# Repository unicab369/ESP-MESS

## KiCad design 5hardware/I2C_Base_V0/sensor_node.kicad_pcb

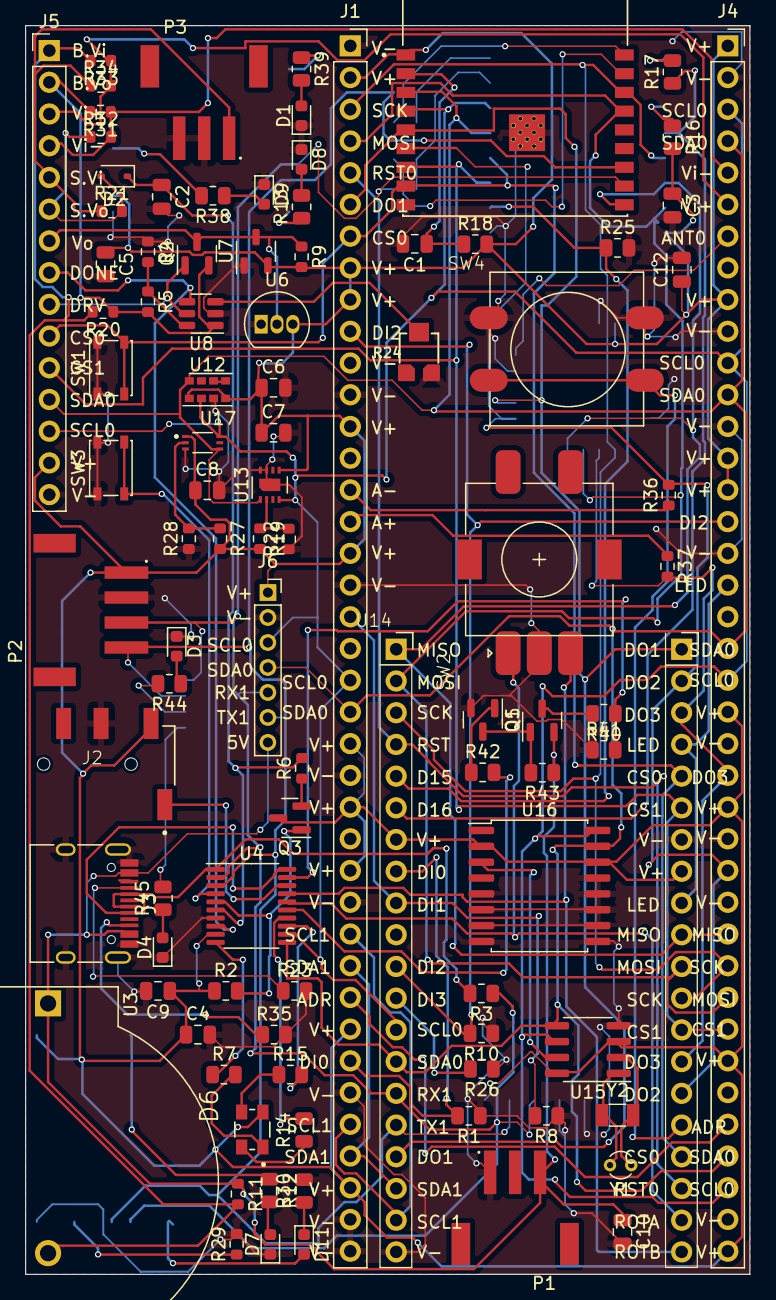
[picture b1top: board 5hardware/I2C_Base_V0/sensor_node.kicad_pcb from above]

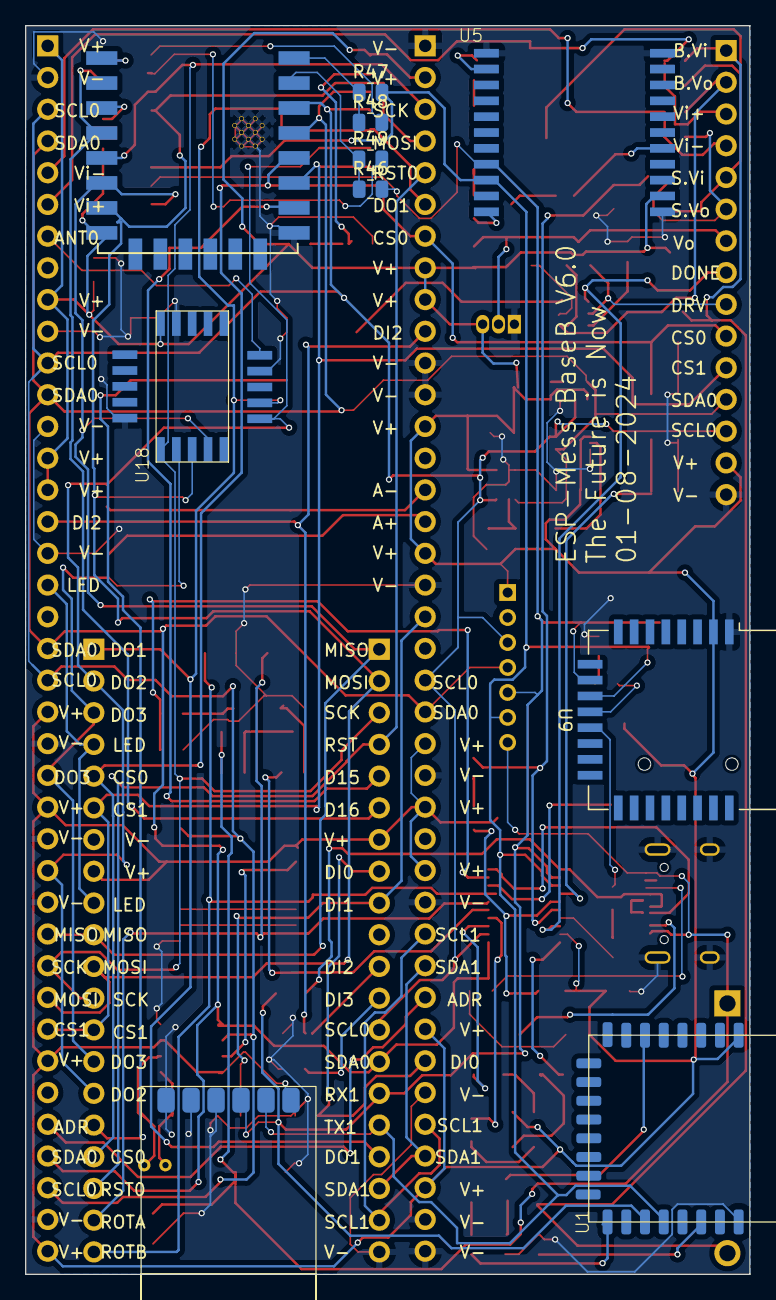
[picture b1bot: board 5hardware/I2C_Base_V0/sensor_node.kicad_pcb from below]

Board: 2 copper layers, 58.0 x 100.0 mm, 106 parts (10 on the bottom side), 91 nets.

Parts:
C1, C2, C3, C4, C5, C6, C7, C8, C9, C10, C12: C; C_0805_2012Metric
D1, D3, D4, D7, D8, D9, D11: LED; LED_0603_1608Metric
D2: D_Schottky; D_SOD-323
D6: LL-R3528RGBC-008-B; LED_LL-R3528RGBC-008-B
J1, J4: Conn_01x39_Socket; PinSocket_1x39_P2.54mm_Vertical
J2: PJ-320D-A; PJ-320D
J3: USB_C_Receptacle_USB2.0; USB_C_Receptacle_HRO_TYPE-C-31-M-12
J5: Conn_01x15_Pin; PinHeader_1x15_P2.54mm_Vertical
J6: Conn_01x07_Pin; PinSocket_1x07_P2.00mm_Vertical
P1, P3: S3B-PH-SM4-TB; JST_S3B-PH-SM4-TB
P2: S4B-PH-SM4-TB; JST_S4B-PH-SM4-TB
Q1, Q2, Q3: Si2371EDS; SOT-23
Q5: MMBT5551L; SOT-23
R1, R2, R3, R7, R8, R10, R12, R13, R14, R15, R16, R17, R18, R23, R25, R26, R30, R35, R38, R39, R40, R41, R42, R43, R44, R45, R46, R47, R48, R49: R; R_0805_2012Metric
R4, R5, R6, R9, R11, R19, R20, R21, R22, R27, R28, R29, R31, R32, R33, R34, R36, R37: R; R_0603_1608Metric
R24: EVM3ESX50B12; EMV3ESX50B12
SW1, SW3: SW_Push; SW_SPST_PTS810
SW2: RotaryEncoder; RotaryEncoder_E11
SW4: SW_Push; ButtonSwitch12mm_SMD
U1: JDY-Base
U2: ESP32-C3-WROOM-02; MODULE_ESP32-C3-WROOM-02-H4
U3: CR2450; BatteryHolder_ComfortableElectronic_CH273-2450_1x2450
U4: CH32V003F4P6; TSSOP-20_4.4x6.5mm_P0.65mm
U5: E104-BT07
U6: MCP1700x-330xxTO; TO-92_Inline
U7: XC6206PxxxMR; SOT-23-3
U8: TPL5110; SOT-23-6
U9: E18-MS1-PCB
U10: ESP-12F; ESP12_SMD
U11: JDY-41
U12: APDS-9960; Avago_APDS-9960
U13: SHT31-DIS; Sensirion_DFN-8-1EP_2.5x2.5mm_P0.5mm_EP1.1x1.7mm
U14: Lolin_Base; LolinBase
U15: DS1307Z+; SOIC-8_3.9x4.9mm_P1.27mm
U16: DS3231M; SOIC-16W_7.5x10.3mm_P1.27mm
U17: BH1750FVI-TR; XDCR_BH1750FVI-TR
U18: E220-900MM
Y1: Crystal; Crystal_Round_D1.5mm_Vertical
Y2: Crystal; Crystal_SMD_3215-2Pin_3.2x1.5mm

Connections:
+5V: C10.1, J3.A4 (VBUS), J3.A9 (VBUS), J3.B4 (VBUS), J3.B9 (VBUS), J6.7, P1.3, Q1.2 (S), R11.1, R43.1, U3.1 (+)
A+: J1.16, R37.1
A-: J1.15, R36.1
ADDR: J1.31, J4.35
ANT0: J4.7, U18.6 (ANT)
Bat-Vi: J5.1, R11.2, R20.2, R33.2, U3.2 (-)
Bat-Vo: J5.2, Q2.2 (S), R5.2, R20.1, R31.2, U8.1 (VDD)
CS0: J1.7, J5.10, SW1.2, U2.8 (GPIO9), U10.12 (GPIO0), U14.25 (X), U14.37 (IO_0)
CS1: J4.32, J5.11, U2.7 (GPIO8), U10.11 (GPIO2), U14.26 (X), U14.33 (IO_5)
D15: R25.1, U10.10 (GPIO15), U14.5 (X)
D16: R17.1, U10.4 (GPIO16), U14.6 (X)
D+: J3.A6 (D+), J3.B6 (D+), U4.20 (PD3)
D-: J3.A7 (D-), J3.B7 (D-), R3.2, U4.1 (PD4)
DI0: J1.33, R1.2, U14.8 (IO_36)
DI1: J1.19, R8.2, U14.9 (IO_39)
DI2: J1.10, J4.16, R10.2, U14.11 (IO_34)
DI3: R26.2, U14.12 (IO_35)
DO1: J1.6, U2.5 (GPIO6), U14.17 (IO_27), U14.21 (X), U18.9 (TXE)
DO2: J4.27, R36.2, U2.6 (GPIO7), U14.22 (X), U14.35 (IO_16), U18.10 (RXE)
DO3: J4.24, R37.2, U14.23 (X), U14.34 (IO_17), U18.14 (CS)
DONE: J5.8, U4.8 (PD0), U8.4 (DONE)
DRV: J5.9, Q2.1 (G), U8.5 (DRV)
EN: R16.1, U10.3 (CH_PD)
GND: C1.2, C2.2, C3.2, C4.2, C5.2, C6.2, C7.2, C8.2, C9.2, C10.2, C12.2, D1.1 (K), D3.1 (K), D4.1 (K), D7.1 (K), D8.1 (K), D9.1 (K), J1.1, J1.11, J1.12, J1.18, J1.24, J1.28, J1.34, J1.38, J1.39, J2.3, J3.A1 (GND), J3.A12 (GND), J3.B1 (GND), J3.B12 (GND), J3.S1 (SHIELD), J4.2, J4.10, J4.13, J4.17, J4.23, J4.26, J4.28, J4.38, J5.15, J6.2, P1.1, P2.2, P3.2, P3.3, Q5.2 (E), R1.1, R4.1, R8.1, R10.1, R22.1, R23.2, R24.3, R25.2, R26.1, R28.1, R29.2, R30.2, R35.2, R41.1, SW1.1, SW2.C, SW3.1, SW4.1, U1.24 (GND), U2.9 (GND), U2.19 (GND), U4.7 (VSS), U5.1 (GND), U5.12 (GND), U5.22 (GND), U6.1 (GND), U7.1 (GND), U8.2 (GND), U9.1 (GND), U10.9 (GND), U11.4 (SET), U11.5 (CS), U11.6 (GND), U12.6 (GND), U13.7 (R), U13.8 (VSS), U13.9 (VSS), U14.20 (GND), U14.27 (X), U15.4 (GND), U16.5 (GND), U16.6 (GND), U16.7 (GND), U16.8 (GND), U16.9 (GND), U16.10 (GND), U16.11 (GND), U16.12 (GND), U16.13 (GND), U17.3 (GND), U18.2 (GND), U18.7 (GND), U18.16 (GND)
LED: J4.18, U14.24 (X), U14.29 (IO_22)
MISO: J4.29, U2.10 (GPIO10), U10.6 (GPIO12), U14.1 (X), U14.30 (IO_19), U18.12 (MISO)
MOSI: J1.4, J4.31, U2.15 (GPIO3/ADC1_CH3), U10.7 (GPIO13), U14.2 (X), U14.31 (IO_23), U18.13 (MOSI)
unnamed: D1.2 (A), R39.2
unnamed: C2.1, D2.1 (K), R6.2, U4.6 (PA2)
unnamed: D3.2 (A), R44.1
unnamed: D4.2 (A), R45.1
unnamed: D6.1, R7.2
unnamed: D6.3, R15.1
unnamed: D6.4, R14.1
unnamed: D7.2 (A), R12.2
unnamed: D8.2 (A), R13.2
unnamed: D9.2 (A), R38.1
unnamed: D11.2 (A), U1.17 (ALED)
unnamed: D11.1 (K), R30.1
unnamed: J3.A5 (CC1), R23.1
unnamed: J3.B5 (CC2), R35.1
unnamed: Q1.3 (D), R40.2
unnamed: Q1.1 (G), Q5.3 (C), R43.2
unnamed: Q3.1 (G), R2.2, U4.5 (PA1)
unnamed: Q3.2 (S), R6.1
unnamed: Q5.1 (B), R42.1
unnamed: R29.1, U1.22 (PWRC)
unnamed: R12.1, U1.6 (STAT)
unnamed: C1.1, R18.1, U2.2 (EN/CHIP_PU)
unnamed: R7.1, U4.10 (PC0)
unnamed: R15.2, U4.13 (PC3)
unnamed: R14.2, U4.14 (PC4)
unnamed: R42.2, U4.15 (PC5)
unnamed: SW3.2, U4.4 (PD7)
unnamed: R38.2, U5.16 (P7)
unnamed: R39.1, U5.2 (P19)
unnamed: R13.1, U5.11 (P32)
unnamed: R24.2, U8.3 (DELAY/M_DRV)
unnamed: R4.2, R5.1, U8.6 (EN/ONE_SHOT)
unnamed: R45.2, U9.13 (P1.2)
unnamed: R44.2, U9.12 (P1.3)
unnamed: R46.1, R49.1, U10.15 (RXD)
unnamed: R47.1, R48.1, U10.16 (TXD)
unnamed: U12.3 (LDR), U12.4 (LED_K)
unnamed: R19.1, R22.2, U13.2 (ADDR)
unnamed: SW4.2, U14.36 (IO_4)
unnamed: U15.7 (SQW/OUT), U16.3 (~INT/SQW)
unnamed: U15.1 (X1), Y1.2, Y2.2
unnamed: U15.2 (X2), Y1.1, Y2.1
unnamed: R27.1, R28.2, U17.2 (ADDR)
PD2: R40.1, R41.2, U4.19 (PD2)
ROTA: SW2.A, U4.16 (PC6), U14.39 (IO_15)
ROTB: SW2.B, U4.17 (PC7), U14.40 (IO_13)
RST0: J1.5, U14.4 (X), U14.38 (IO_2)
RST1: R17.2, U10.1 (REST)
RX1: J6.5, P2.3, R3.1, R46.2, U1.19 (TX), U2.11 (GPIO20/U0RXD), U4.2 (PD5), U5.8 (TX), U9.10 (P1.5), U11.3 (TX), U14.15 (IO_25)
RX2: R48.2, U2.18 (GPIO0/ADC1_CH0/XTAL_32K_P)
SCK: J1.3, J4.30, U2.16 (GPIO2/ADC1_CH2), U10.5 (GPIO14), U14.3 (X), U14.32 (IO_18), U18.15 (SCK)
SCL0: J1.21, J4.3, J4.11, J4.21, J4.37, J5.13, J6.3, U2.4 (GPIO5/ADC2_CH0), U4.12 (PC2), U10.14 (GPIO5), U12.7 (SCL), U13.4 (SCL), U14.13 (IO_32), U15.6 (SCL), U16.16 (SCL), U17.6 (SCL)
SCL1: J1.29, J1.35, U14.19 (IO_12)
SDA0: J1.22, J4.4, J4.12, J4.20, J4.36, J5.12, J6.4, U2.3 (GPIO4/ADC1_CH4), U4.11 (PC1), U10.13 (GPIO4), U12.1 (SDA), U13.1 (SDA), U14.14 (IO_33), U15.5 (SDA), U16.15 (SDA), U17.4 (SDA)
SDA1: J1.30, J1.36, U14.18 (IO_14)
SWIO: J2.1, U4.18 (PD1)
Solar_Vi: J5.5, P3.1, R21.1, R34.1
Solar_Vo: D2.2 (A), J5.6, R21.2, R32.1
TX1: J6.6, P2.4, R47.2, U1.20 (RX), U2.12 (GPIO21/U0TXD), U4.3 (PD6), U5.9 (RX), U9.11 (P1.4), U11.2 (RX), U14.16 (IO_26)
TX2: R49.2, U2.17 (GPIO1/ADC1_CH1/XTAL_32K_N)
VCC: C3.1, C4.1, C5.1, C6.1, C7.1, C8.1, C9.1, C12.1, D6.2, J1.2, J1.8, J1.9, J1.13, J1.17, J1.23, J1.25, J1.27, J1.32, J1.37, J2.2, J4.1, J4.9, J4.14, J4.15, J4.22, J4.25, J4.33, J4.39, J5.14, J6.1, P2.1, Q3.3 (D), R2.1, R9.2, R16.2, R18.2, R19.2, R27.2, U1.1 (VCC), U2.1 (3V3), U4.9 (VDD), U5.13 (VDD), U6.3 (VO), U7.2 (VO), U9.2 (VDD), U10.8 (VCC), U11.1 (VCC), U12.5 (LED_A), U12.8 (VCC), U13.5 (VDD), U14.7 (X), U14.28 (VCC), U15.3 (VBAT), U15.8 (VCC), U16.2 (VCC), U16.14 (VBAT), U17.1 (VCC), U18.1 (VCC)
Vi+: J4.6, J5.3, R33.1, R34.2
Vi-: J4.5, J5.4, R31.1, R32.2
Vo: J5.7, Q2.3 (D), R9.1, U6.2 (VI), U7.3 (VI)

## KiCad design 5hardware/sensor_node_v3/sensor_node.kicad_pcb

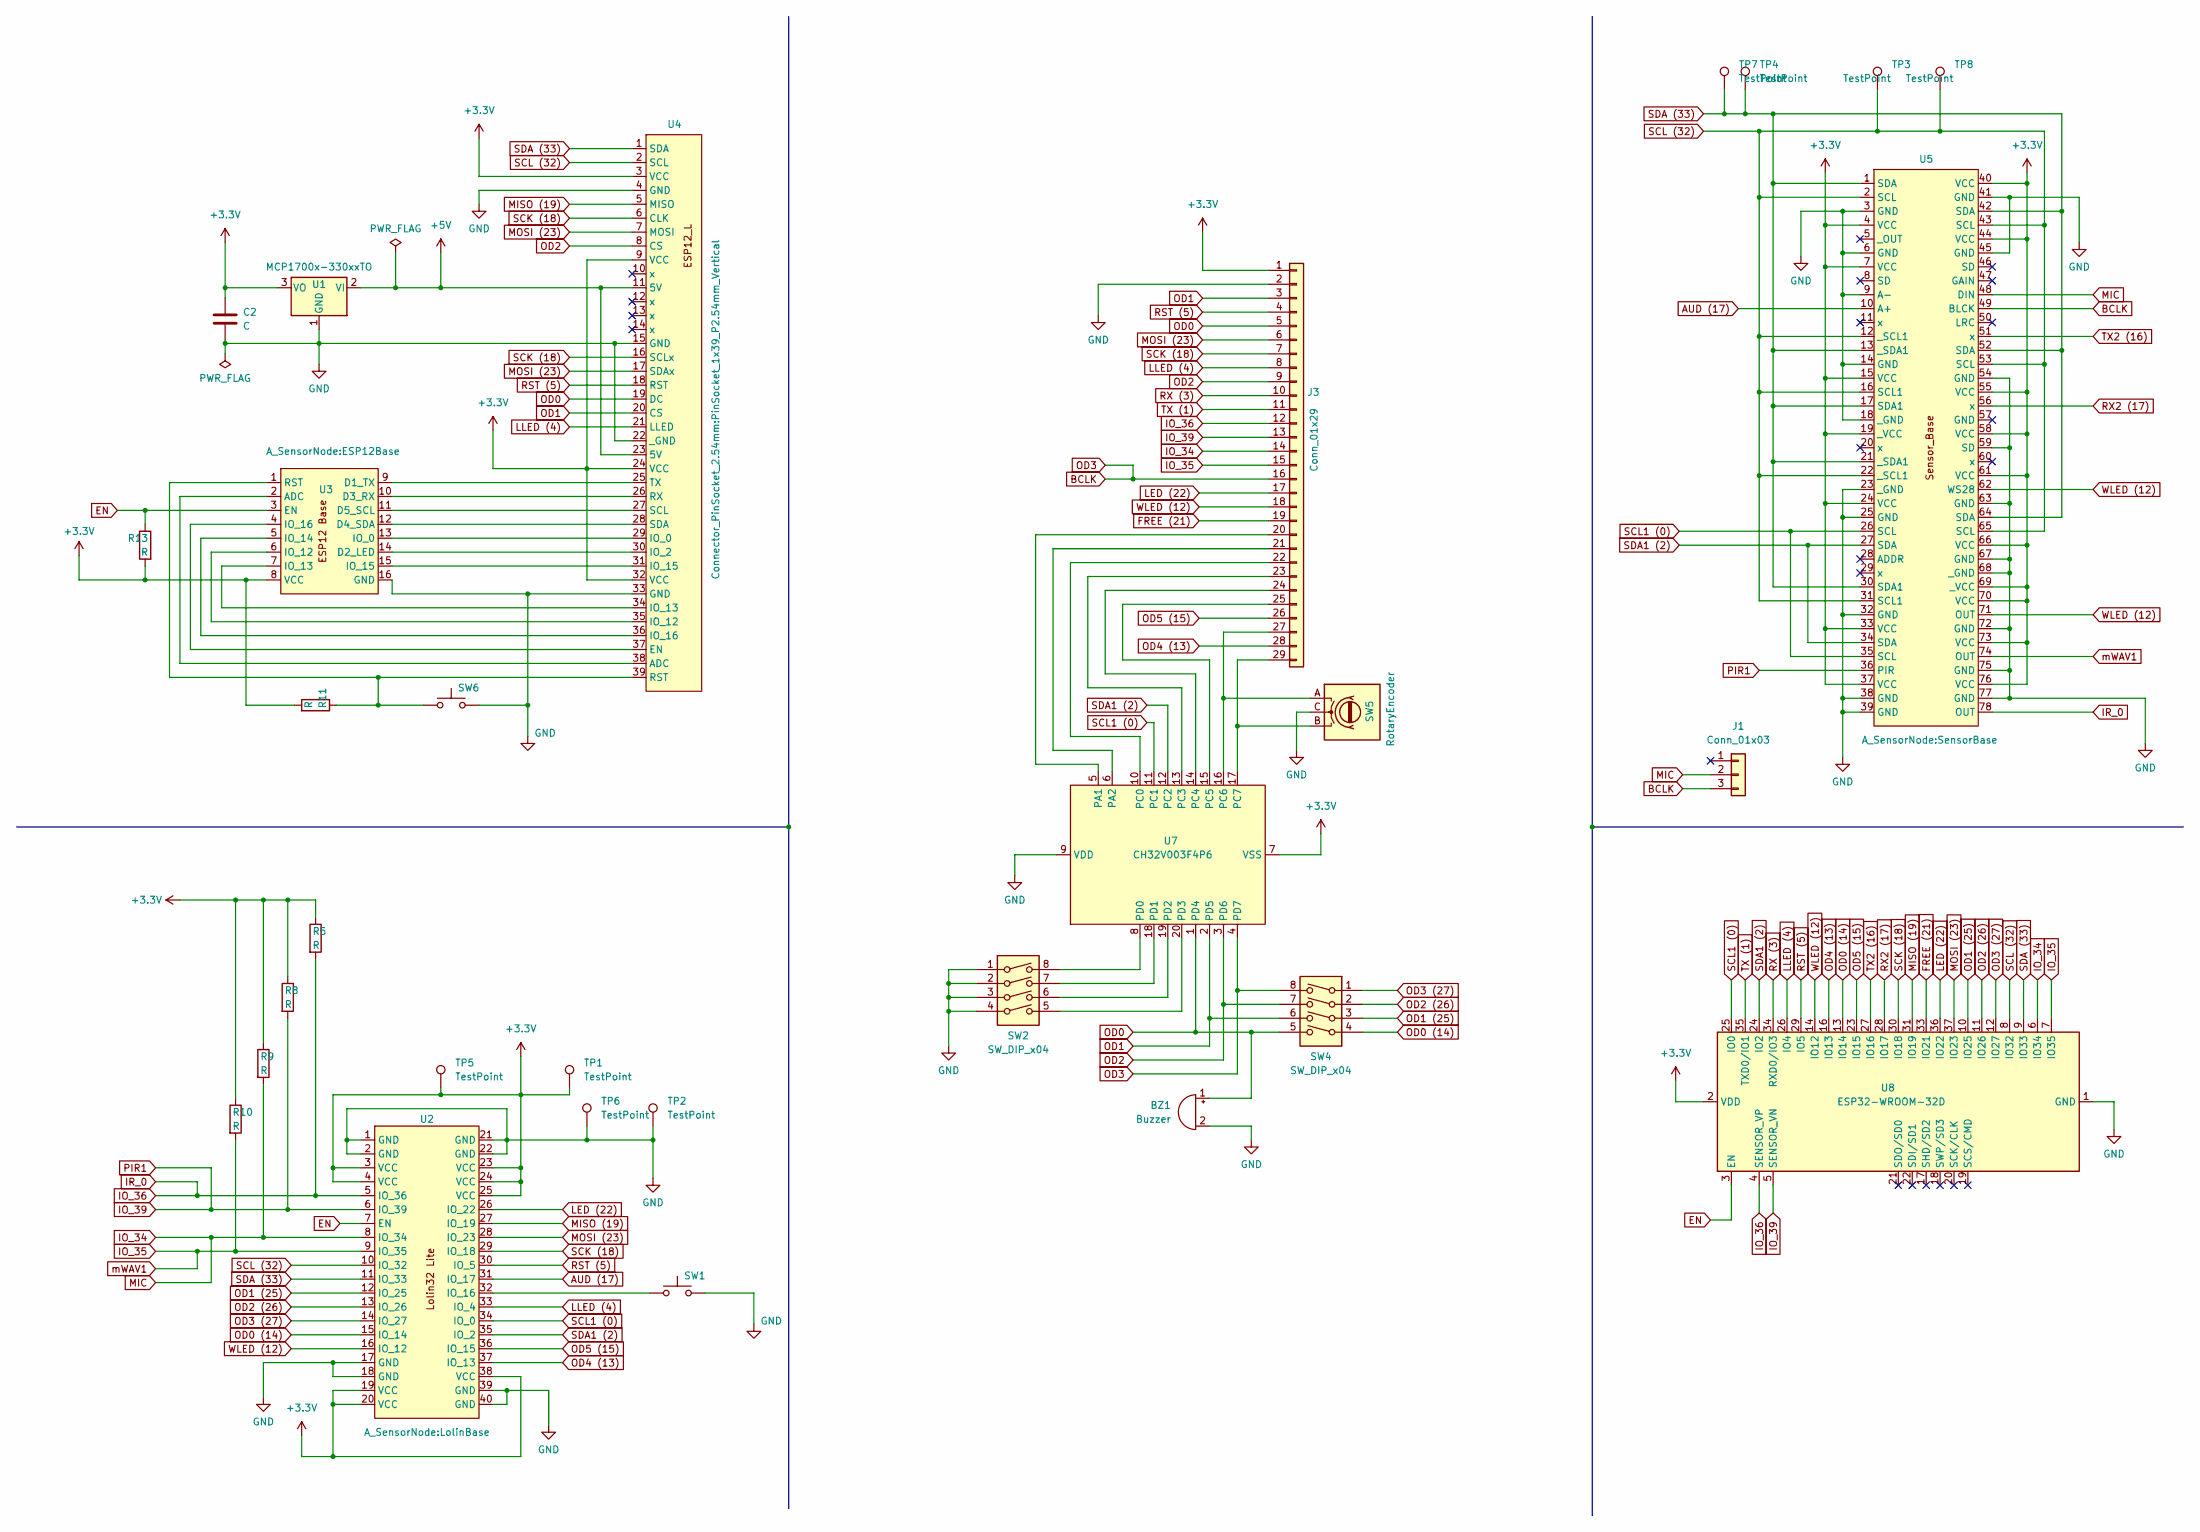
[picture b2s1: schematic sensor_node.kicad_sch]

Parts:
BZ1: Buzzer; BuzzerSmall
C2: C; CP_Radial_D5.0mm_P2.00mm
J1: Conn_01x03; PinHeader_1x03_P2.54mm_Vertical
J3: Conn_01x29; PinSocket_1x29_P2.54mm_Vertical
R5, R8, R9, R10, R11, R13: R; R_2512_6332Metric
SW1: SW_Push; SW_PUSH-12mm
SW2, SW4: SW_DIP_x04; SW_DIP_SPSTx04_Slide_6.7x11.72mm_W8.61mm_P2.54mm_LowProfile
SW5: RotaryEncoder; RotaryEncoder_Alps_EC11E_Vertical_H20mm
SW6: SW_Push; SW_PUSH_6mm_H7.3mm
TP1, TP2, TP3, TP4, TP5, TP6, TP7, TP8: TestPoint; TestPoint_Pad_1.5x1.5mm
U1: MCP1700x-330xxTO; TO-92_Inline
U2: LolinBase
U3: ESP12Base
U4: PinSocket_1x39_P2.54mm_Vertical
U5: SensorBase
U7: CH32V003F4P6; TSSOP-20_4.4x6.5mm_P0.65mm
U8: ESP32-WROOM-32D; ESP32-WROOM-32D2

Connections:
+3.3V: C2.1, J3.1, R5.1, R8.1, R9.1, R10.1, R11.2, R13.2, TP1.1, TP5.1, U1.3 (VO), U2.3 (VCC), U2.4 (VCC), U2.19 (VCC), U2.20 (VCC), U2.23 (VCC), U2.24 (VCC), U2.25 (VCC), U2.38 (VCC), U3.8 (VCC), U4.3 (VCC), U4.9 (VCC), U4.24 (VCC), U4.32 (VCC), U5.4 (VCC), U5.7 (VCC), U5.15 (VCC), U5.19 (_VCC), U5.24 (VCC), U5.33 (VCC), U5.37 (VCC), U5.40 (VCC), U5.44 (VCC), U5.55 (VCC), U5.58 (VCC), U5.61 (VCC), U5.66 (VCC), U5.69 (_VCC), U5.70 (VCC), U5.73 (VCC), U5.76 (VCC), U7.7 (VSS), U8.2 (VDD)
+5V: U1.2 (VI), U4.11 (5V), U4.23 (5V)
AUD (17): U2.31 (IO_17), U5.10 (A+)
BCLK: J1.3, J3.16, SW4.8, U5.49 (BLCK), U7.4 (PD7)
EN: R13.1, U2.7 (EN), U3.3 (EN), U8.3 (EN)
FREE (21): J3.19, U8.33 (IO21)
GND: BZ1.2 (+), C2.2, J3.2, SW1.1, SW2.1, SW2.2, SW2.3, SW2.4, SW5.C, SW6.1, TP2.1, TP6.1, U1.1 (GND), U2.1 (GND), U2.2 (GND), U2.17 (GND), U2.18 (GND), U2.21 (GND), U2.22 (GND), U2.39 (GND), U2.40 (GND), U3.16 (GND), U4.4 (GND), U4.15 (GND), U4.22 (_GND), U4.33 (GND), U5.3 (GND), U5.6 (GND), U5.9 (A-), U5.14 (GND), U5.18 (_GND), U5.23 (_GND), U5.25 (GND), U5.32 (GND), U5.38 (GND), U5.39 (GND), U5.41 (GND), U5.45 (GND), U5.54 (GND), U5.59 (SD), U5.63 (GND), U5.67 (GND), U5.68 (_GND), U5.72 (GND), U5.75 (GND), U5.77 (GND), U7.9 (VDD), U8.1 (GND), U8.15 (GND), U8.38 (GND), U8.39 (GND)
IO_34: J1.2, J3.14, R9.2, U2.8 (IO_34), U5.48 (DIN), U8.6 (IO34)
IO_35: J3.15, R10.2, U2.9 (IO_35), U5.74 (OUT), U8.7 (IO35)
IO_36: J3.12, R5.2, U2.5 (IO_36), U5.78 (OUT), U8.4 (SENSOR_VP)
IO_39: J3.13, R8.2, U2.6 (IO_39), U5.36 (PIR), U8.5 (SENSOR_VN)
LED (22): J3.17, U2.26 (IO_22), U8.36 (IO22)
LLED (4): J3.8, U2.33 (IO_4), U4.21 (LLED), U8.26 (IO4)
MISO (19): U2.27 (IO_19), U4.5 (MISO), U8.31 (IO19)
MOSI (23): J3.6, U2.28 (IO_23), U4.7 (MOSI), U4.17 (SDAx), U8.37 (IO23)
unnamed: J3.20, U7.5 (PA1)
unnamed: J3.21, U7.6 (PA2)
unnamed: J3.22, U7.10 (PC0)
unnamed: J3.23, U7.13 (PC3)
unnamed: J3.24, U7.14 (PC4)
unnamed: J3.25, U7.15 (PC5)
unnamed: J3.27, SW5.A, U7.16 (PC6)
unnamed: J3.29, SW5.B, U7.17 (PC7)
unnamed: SW1.2, U2.32 (IO_16)
unnamed: U3.2 (ADC), U4.38 (ADC)
unnamed: U3.9 (D1_TX), U4.25 (TX)
unnamed: U3.14 (D2_LED), U4.30 (IO_2)
unnamed: U3.10 (D3_RX), U4.26 (RX)
unnamed: U3.12 (D4_SDA), U4.28 (SDA)
unnamed: U3.11 (D5_SCL), U4.27 (SCL)
unnamed: U3.13 (IO_0), U4.29 (IO_0)
unnamed: U3.6 (IO_12), U4.35 (IO_12)
unnamed: U3.7 (IO_13), U4.34 (IO_13)
unnamed: U3.5 (IO_14), U4.36 (IO_16)
unnamed: U3.15 (IO_15), U4.31 (IO_15)
unnamed: U3.4 (IO_16), U4.37 (EN)
unnamed: R11.1, SW6.2, U3.1 (RST), U4.39 (RST)
unnamed: SW2.8, U7.8 (PD0)
unnamed: SW2.7, U7.18 (PD1)
unnamed: SW2.6, U7.19 (PD2)
unnamed: SW2.5, U7.20 (PD3)
OD0: BZ1.1 (-), J3.5, SW4.5, U4.19 (DC), U7.1 (PD4)
OD0 (14): SW4.4, U2.15 (IO_14), U8.13 (IO14)
OD1: J3.3, SW4.6, U4.20 (CS), U7.2 (PD5)
OD1 (25): SW4.3, U2.12 (IO_25), U8.10 (IO25)
OD2: J3.9, SW4.7, U4.8 (CS), U7.3 (PD6)
OD2 (26): SW4.2, U2.13 (IO_26), U8.11 (IO26)
OD3 (27): SW4.1, U2.14 (IO_27), U8.12 (IO27)
OD4 (13): J3.28, U2.37 (IO_13), U8.16 (IO13)
OD5 (15): J3.26, U2.36 (IO_15), U8.23 (IO15)
RST (5): J3.4, U2.30 (IO_5), U4.18 (RST), U8.29 (IO5)
RX2 (17): U5.56 (x), U8.28 (IO17)
RX (3): J3.10, U8.34 (RXD0/IO3)
SCK (18): J3.7, U2.29 (IO_18), U4.6 (CLK), U4.16 (SCLx), U8.30 (IO18)
SCL1 (0): U2.34 (IO_0), U5.26 (SCL), U5.35 (SCL), U7.11 (PC1), U8.25 (IO0)
SCL (32): TP3.1, TP8.1, U2.10 (IO_32), U4.2 (SCL), U5.2 (SCL), U5.12 (_SCL1), U5.16 (SCL1), U5.22 (_SCL1), U5.31 (SCL1), U5.43 (SCL), U5.53 (SCL), U5.65 (SCL), U8.8 (IO32)
SDA1 (2): U2.35 (IO_2), U5.27 (SDA), U5.34 (SDA), U7.12 (PC2), U8.24 (IO2)
SDA (33): TP4.1, TP7.1, U2.11 (IO_33), U4.1 (SDA), U5.1 (SDA), U5.13 (_SDA1), U5.17 (SDA1), U5.21 (_SDA1), U5.30 (SDA1), U5.42 (SDA), U5.52 (SDA), U5.64 (SDA), U8.9 (IO33)
TX2 (16): U5.51 (x), U8.27 (IO16)
TX (1): J3.11, U8.35 (TXD0/IO1)
WLED (12): J3.18, U2.16 (IO_12), U5.62 (WS28), U5.71 (OUT), U8.14 (IO12)

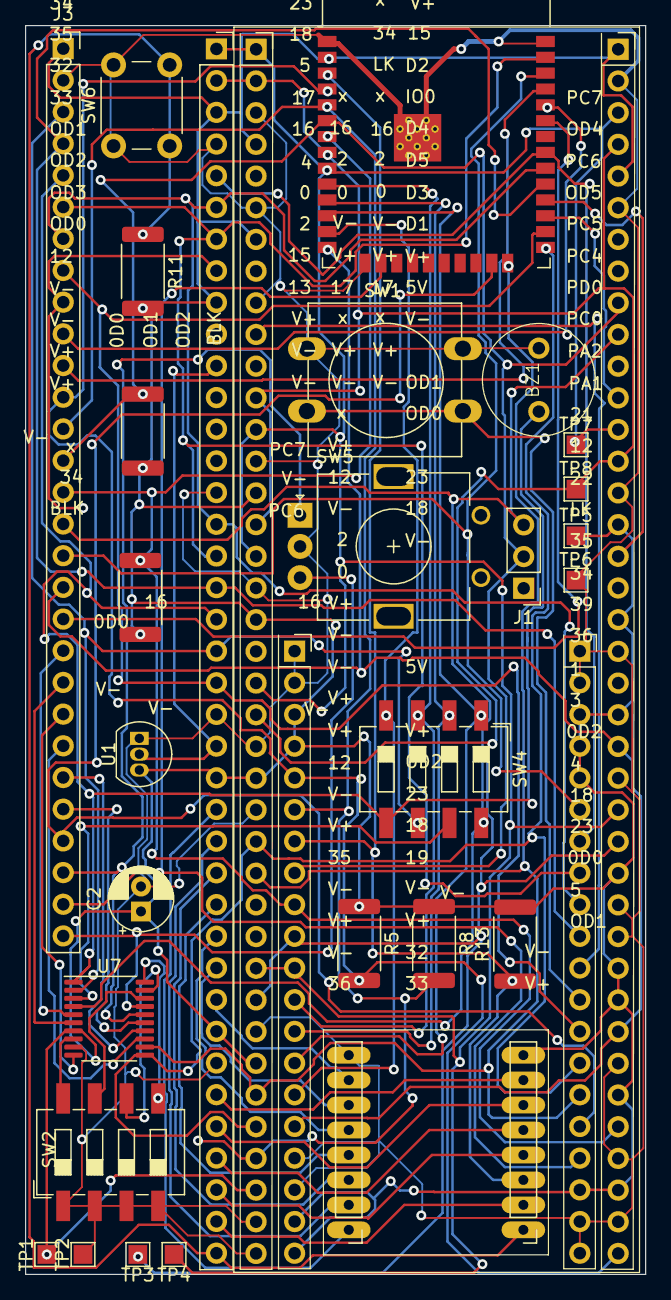
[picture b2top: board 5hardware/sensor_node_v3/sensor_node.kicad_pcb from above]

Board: 2 copper layers, 49.7 x 100.1 mm, 30 parts (0 on the bottom side), 61 nets.

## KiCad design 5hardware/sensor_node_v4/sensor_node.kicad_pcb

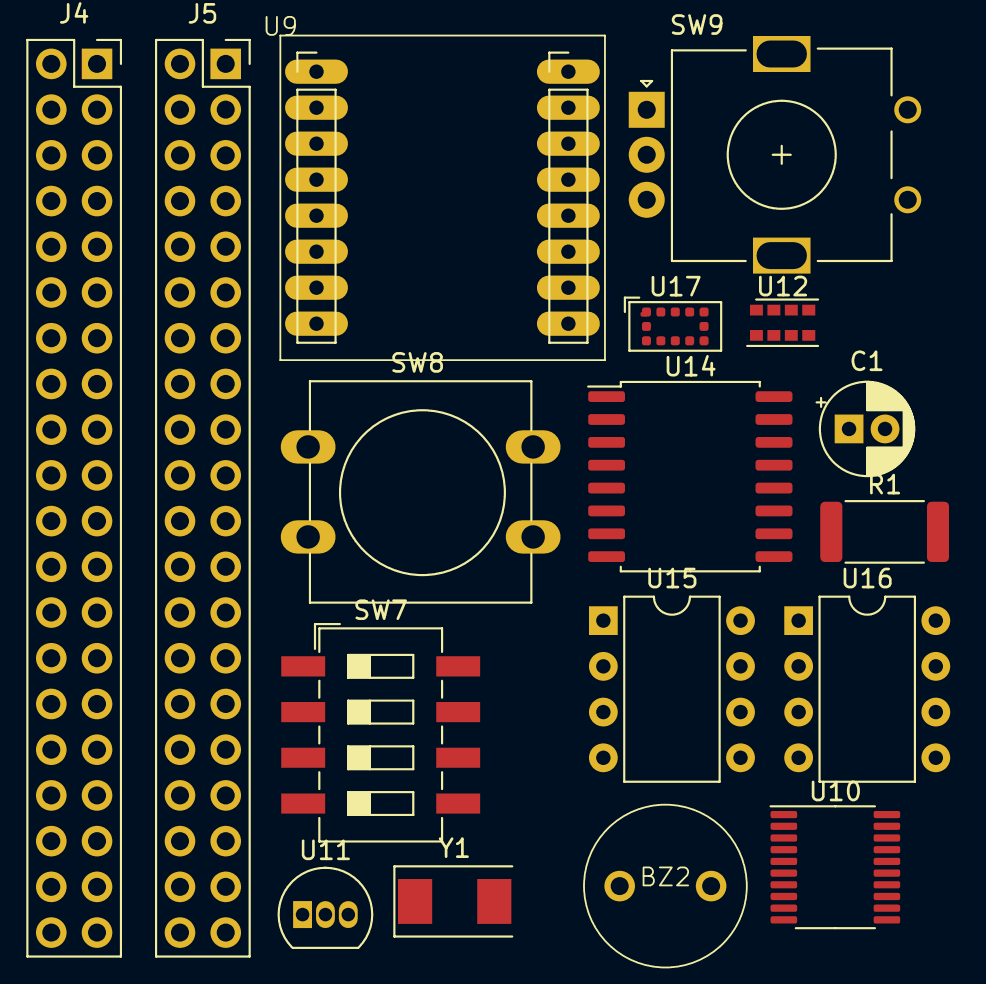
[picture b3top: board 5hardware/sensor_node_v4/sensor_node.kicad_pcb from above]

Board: 2 copper layers, 17 parts (0 on the bottom side), 29 nets, no tracks yet.

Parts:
BZ2: Buzzer; BuzzerSmall
C1: C; CP_Radial_D5.0mm_P2.00mm
J4, J5: Conn_02x20_Counter_Clockwise; PinSocket_2x20_P2.54mm_Vertical
R1: R; R_2512_6332Metric
SW7: SW_DIP_x04; SW_DIP_SPSTx04_Slide_6.7x11.72mm_W8.61mm_P2.54mm_LowProfile
SW8: SW_Push; SW_PUSH-12mm
SW9: RotaryEncoder; RotaryEncoder_Alps_EC11E_Vertical_H20mm
U9: ESP12Base
U10: CH32V003F4P6; TSSOP-20_4.4x6.5mm_P0.65mm
U11: MCP1700x-330xxTO; TO-92_Inline
U12: APDS-9960; Avago_APDS-9960
U14: DS3231M; SOIC-16W_7.5x10.3mm_P1.27mm
U15: DS1307+; DIP-8_W7.62mm
U16: DS1302+; DIP-8_W7.62mm
U17: VL53L1CXV0FY1; ST_VL53L1x
Y1: Crystal; Crystal_SMD_0603-2Pin_6.0x3.5mm

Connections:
+3.3V: C1.1, R1.2, U9.8 (VCC), U10.7 (VSS), U11.3 (VO), U14.2 (VCC), U15.8 (VCC)
CS_A (11): J4.2, J5.8
EN: R1.1, U9.3 (EN)
GND: BZ2.2 (+), C1.2, J4.8, J4.20, J4.23, J4.26, J4.32, J4.37, J5.9, J5.14, J5.15, J5.21, J5.22, J5.23, J5.24, J5.25, J5.26, SW7.5, SW7.6, SW7.7, SW7.8, SW8.1, SW9.C, U9.16 (GND), U10.9 (VDD), U11.1 (GND), U12.6 (GND), U15.4 (GND), U16.4 (GND), U17.3 (GND), U17.4 (GND), U17.6 (GND), U17.12 (GND)
LLED (19): J4.1, J5.3
MISO_PC7: J5.36, U10.17 (PC7)
MOSI (3): J4.5, J5.5, J5.18
MOSI_PC6: J5.35, U10.16 (PC6)
unnamed: J5.37, SW9.B, U10.13 (PC3)
unnamed: J5.39, SW9.A, U10.14 (PC4)
unnamed: SW7.4, U10.8 (PD0)
unnamed: SW7.3, U10.19 (PD2)
unnamed: SW7.2, U10.20 (PD3)
unnamed: SW7.1, U10.1 (PD4)
unnamed: U14.5 (GND), U14.6 (GND), U14.7 (GND), U14.8 (GND), U14.9 (GND), U14.10 (GND), U14.11 (GND), U14.12 (GND), U14.13 (GND)
unnamed: U14.14 (VBAT), U15.3 (VBAT), U16.1 (VCC2)
unnamed: U14.3 (~INT/SQW), U15.7 (SQW/OUT)
unnamed: U15.1 (X1), U16.2 (X1), Y1.2
unnamed: U15.2 (X2), U16.3 (X2), Y1.1
RST: J5.7, U9.1 (RST)
RX_PD6: J5.31, U10.3 (PD6)
SCK (2): J4.6, J5.4, J5.17
SCK_PC5: J5.34, U10.15 (PC5)
SCL2 (6): J5.33, U10.12 (PC2)
SCL (5): J4.39, U9.11 (D5_SCL), U12.7 (SCL), U14.16 (SCL), U15.6 (SCL), U17.10 (SCL)
SDA2 (7): J5.32, U10.11 (PC1)
SDA (4): J4.40, U9.12 (D4_SDA), U12.1 (SDA), U14.15 (SDA), U15.5 (SDA), U17.9 (SDA)
TX_PD5: J5.30, U10.2 (PD5)
VCC: J4.7, J4.18, J4.24, J4.25, J4.33, J4.38, J5.10, J5.12, J5.20

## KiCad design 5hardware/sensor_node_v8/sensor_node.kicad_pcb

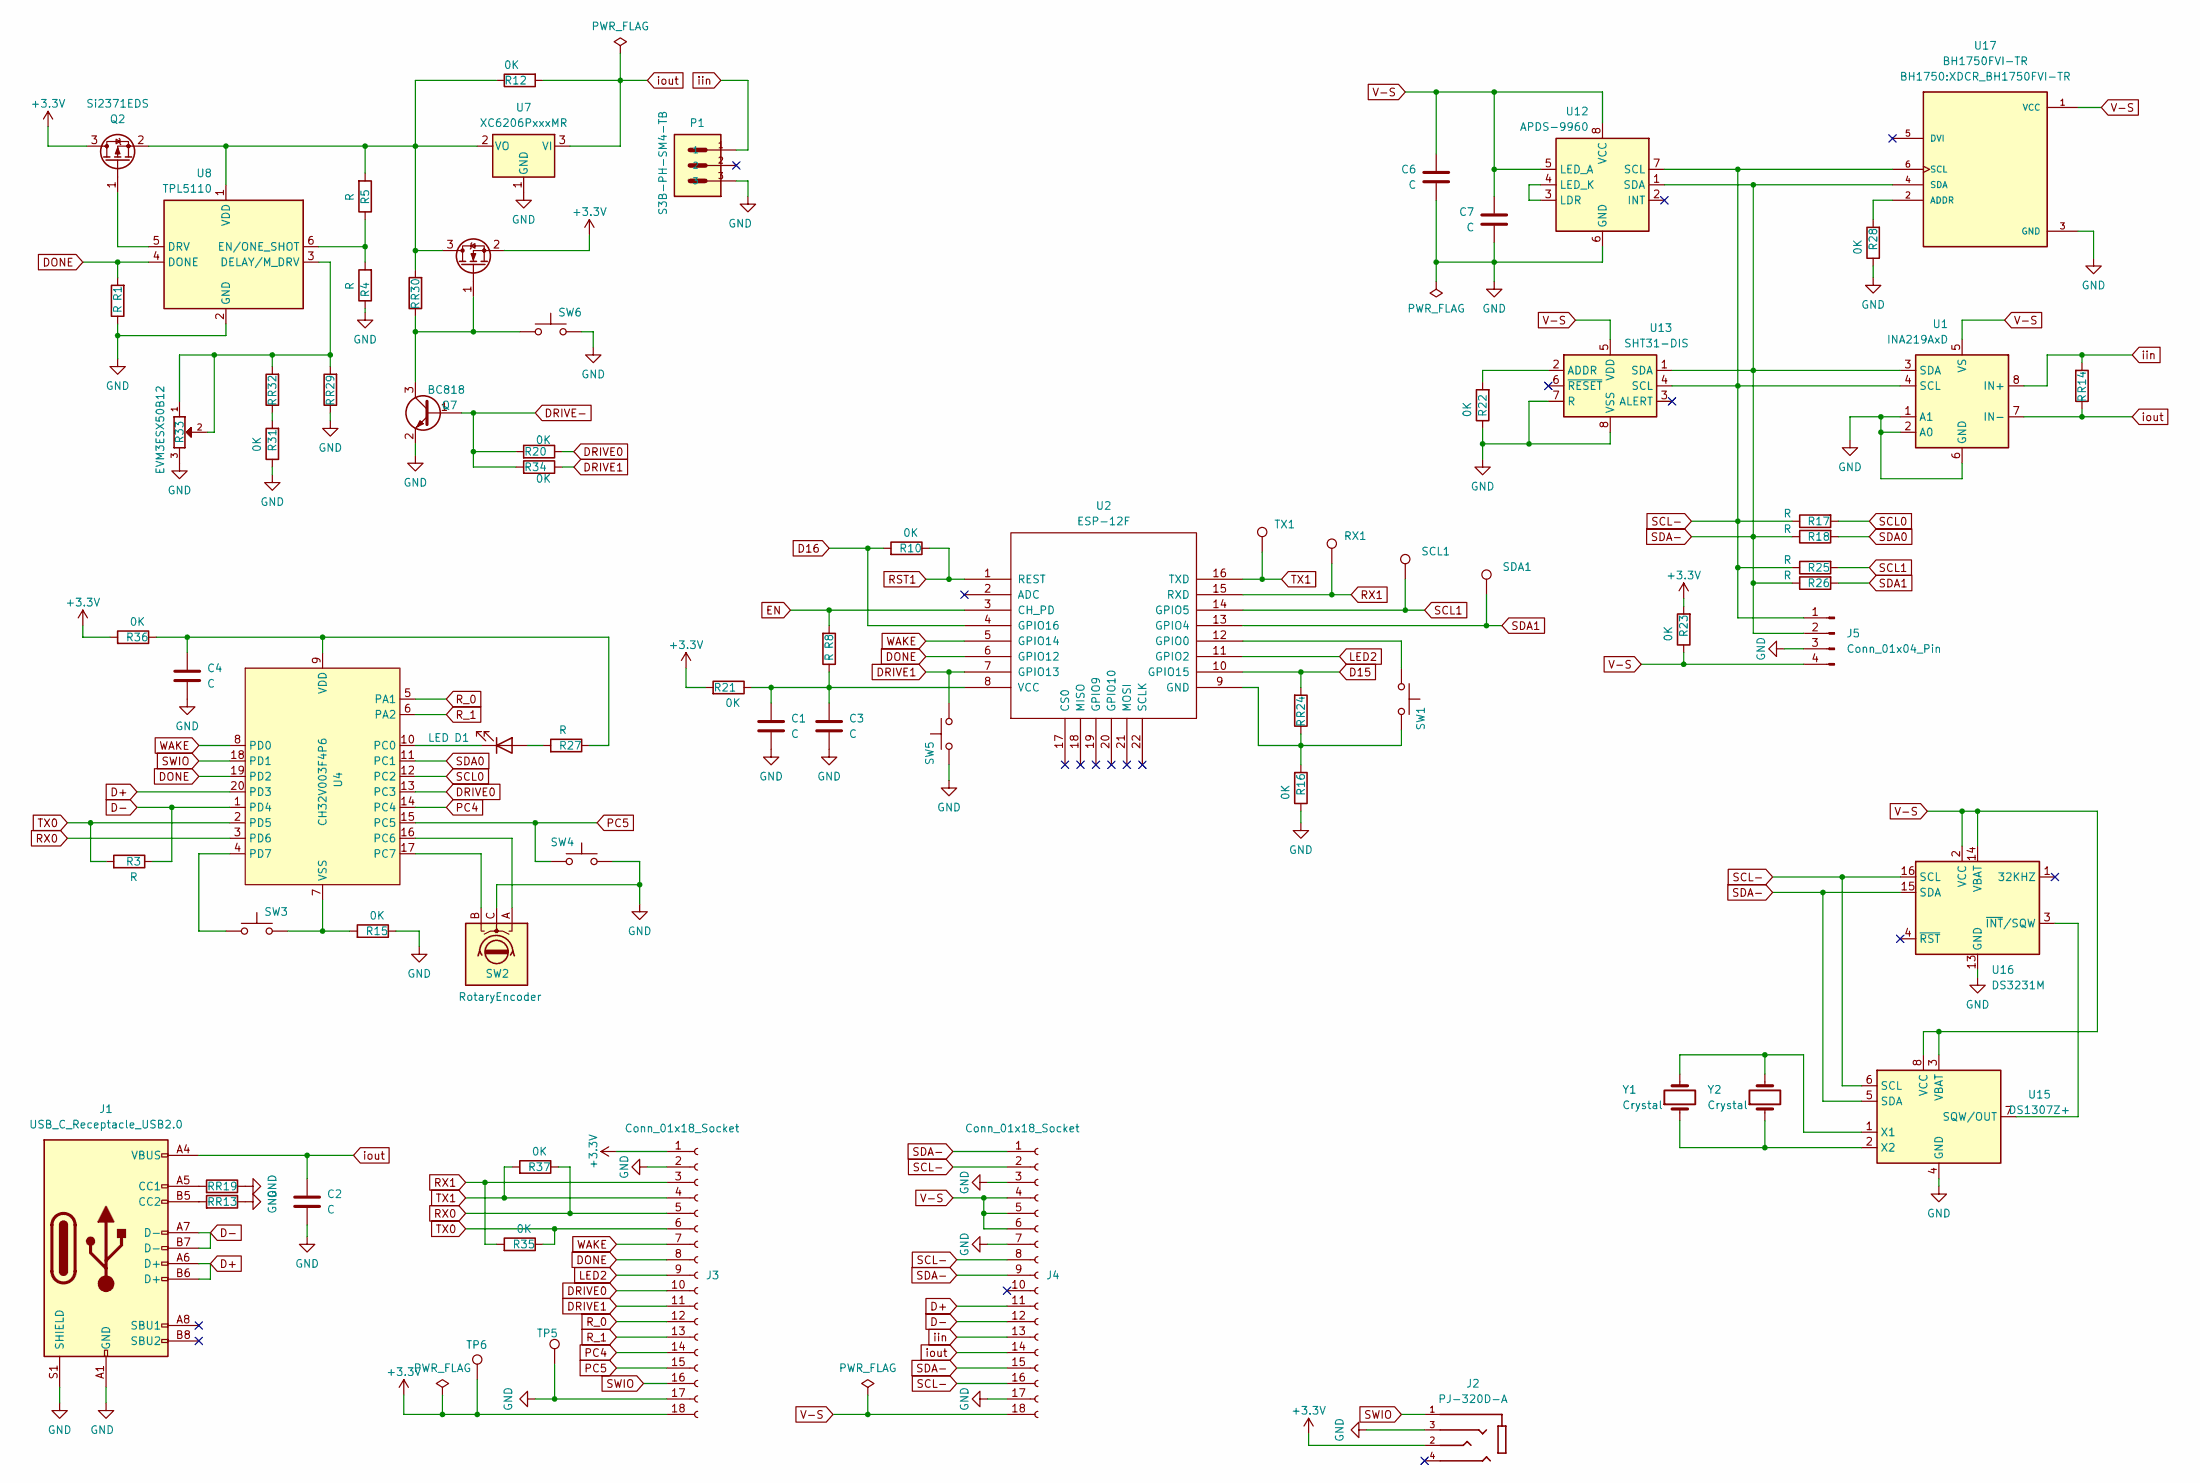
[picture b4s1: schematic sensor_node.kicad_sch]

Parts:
C1, C2, C3, C4, C6, C7: C; C_0603_1608Metric
D1: LED; LED_0603_1608Metric
J1: USB_C_Receptacle_USB2.0; USB_C_Receptacle_HRO_TYPE-C-31-M-12
J2: PJ-320D-A; PJ-320D; PARTREV B
J3, J4: Conn_01x18_Socket; PinSocket_1x18_P2.54mm_Vertical
J5: Conn_01x04_Pin; PinSocket_1x04_P2.54mm_Vertical
P1: S3B-PH-SM4-TB; JST_S3B-PH-SM4-TB
Q2: Si2371EDS; SOT-23
Q6: AO3400A; SOT-23
Q7: BC818; SOT-23
R1, R3, R4, R5, R8, R13, R17, R18, R19, R24, R25, R26, R27, R29, R30, R32: R; R_0603_1608Metric
R10, R12, R15, R16, R20, R21, R22, R23, R28, R31, R34, R35, R36, R37: 0K; R_0603_1608Metric
R14: R; R_2512_6332Metric
R33: EVM3ESX50B12; EMV3ESX50B12
RX1: TestPoint; testpoint
SCL1: TestPoint; testpoint
SDA1: TestPoint; testpoint
SW1, SW3, SW4, SW5, SW6: SW_Push; SW_SPST_PTS810
SW2: RotaryEncoder; RotaryEncoder_E11
TP5, TP6: TestPoint; testpoint
TX1: TestPoint; testpoint
U1: INA219AxD; SOIC-8_3.9x4.9mm_P1.27mm
U2: ESP-12F; ESP12_SMD
U4: CH32V003F4P6; TSSOP-20_4.4x6.5mm_P0.65mm
U7: XC6206PxxxMR; SOT-23-3
U8: TPL5110; SOT-23-6
U12: APDS-9960; Avago_APDS-9960
U13: SHT31-DIS; Sensirion_DFN-8-1EP_2.5x2.5mm_P0.5mm_EP1.1x1.7mm
U15: DS1307Z+; SOIC-8_3.9x4.9mm_P1.27mm
U16: DS3231M; SOIC-16W_7.5x10.3mm_P1.27mm
U17: BH1750FVI-TR; XDCR_BH1750FVI-TR; PARTREV D
Y1: Crystal; Crystal_Round_D1.5mm_Vertical
Y2: Crystal; Crystal_SMD_3215-2Pin_3.2x1.5mm

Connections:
+3.3V: J2.2, J3.1, J3.18, Q2.3 (D), Q6.2 (S), R21.2, R23.2, R36.2, TP6.1
D15: R24.2, U2.10 (GPIO15)
D16: R10.2, U2.4 (GPIO16)
D+: J1.A6 (D+), J1.B6 (D+), J4.11, U4.20 (PD3)
D-: J1.A7 (D-), J1.B7 (D-), J4.12, R3.1, U4.1 (PD4)
DONE: J3.8, R1.2, U2.6 (GPIO12), U4.19 (PD2), U8.4 (DONE)
DRIVE0: J3.10, R20.1, U4.13 (PC3)
DRIVE1: J3.11, R34.1, SW5.2, U2.7 (GPIO13)
DRIVE-: Q7.1 (B), R20.2, R34.2
EN: R8.2, U2.3 (CH_PD)
GND: C1.2, C2.2, C3.2, C4.2, C6.2, C7.2, J1.A1 (GND), J1.A12 (GND), J1.B1 (GND), J1.B12 (GND), J1.S1 (SHIELD), J2.3, J3.2, J3.17, J4.3, J4.7, J4.17, J5.3, P1.3, Q7.2 (E), R1.1, R4.1, R13.1, R15.1, R16.1, R19.1, R22.1, R28.1, R29.1, R31.1, R33.3, SW2.C, SW4.2, SW5.1, SW6.1, TP5.1, U1.1 (A1), U1.2 (A0), U1.6 (GND), U7.1 (GND), U8.2 (GND), U12.6 (GND), U13.7 (R), U13.8 (VSS), U13.9 (VSS), U15.4 (GND), U16.5 (GND), U16.6 (GND), U16.7 (GND), U16.8 (GND), U16.9 (GND), U16.10 (GND), U16.11 (GND), U16.12 (GND), U16.13 (GND), U17.3 (GND)
LED2: J3.9, U2.11 (GPIO2)
unnamed: D1.2 (A), R27.2
unnamed: D1.1 (K), U4.10 (PC0)
unnamed: J1.A5 (CC1), R19.2
unnamed: J1.B5 (CC2), R13.2
unnamed: Q2.1 (G), U8.5 (DRV)
unnamed: Q2.2 (S), Q6.3 (D), R5.2, R12.1, R30.2, U7.2 (VO), U8.1 (VDD)
unnamed: Q6.1 (G), Q7.3 (C), R30.1, SW6.2
unnamed: R31.2, R32.1
unnamed: R16.2, R24.1, SW1.1, U2.9 (GND)
unnamed: SW1.2, U2.12 (GPIO0)
unnamed: C1.1, C3.1, R8.1, R21.1, U2.8 (VCC)
unnamed: SW2.A, U4.16 (PC6)
unnamed: SW2.B, U4.17 (PC7)
unnamed: SW3.2, U4.4 (PD7)
unnamed: C4.1, R27.1, R36.1, U4.9 (VDD)
unnamed: R15.2, SW3.1, U4.7 (VSS)
unnamed: R29.2, R32.2, R33.1, R33.2, U8.3 (DELAY/M_DRV)
unnamed: R4.2, R5.1, U8.6 (EN/ONE_SHOT)
unnamed: U12.3 (LDR), U12.4 (LED_K)
unnamed: R22.2, U13.2 (ADDR)
unnamed: U15.7 (SQW/OUT), U16.3 (~INT/SQW)
unnamed: U15.1 (X1), Y1.2, Y2.2
unnamed: U15.2 (X2), Y1.1, Y2.1
unnamed: R28.2, U17.2 (ADDR)
PC4: J3.14, U4.14 (PC4)
PC5: J3.15, SW4.1, U4.15 (PC5)
RST1: R10.1, U2.1 (REST)
RX0: J3.5, R37.1, U4.3 (PD6)
RX1: J3.3, R35.2, RX1.1, U2.15 (RXD)
R_0: J3.12, U4.5 (PA1)
R_1: J3.13, U4.6 (PA2)
SCL0: R17.2, U4.12 (PC2)
SCL1: R25.2, SCL1.1, U2.14 (GPIO5)
SCL-: J4.2, J4.8, J4.16, J5.1, R17.1, R25.1, U1.4 (SCL), U12.7 (SCL), U13.4 (SCL), U15.6 (SCL), U16.16 (SCL), U17.6 (SCL)
SDA0: R18.2, U4.11 (PC1)
SDA1: R26.2, SDA1.1, U2.13 (GPIO4)
SDA-: J4.1, J4.9, J4.15, J5.2, R18.1, R26.1, U1.3 (SDA), U12.1 (SDA), U13.1 (SDA), U15.5 (SDA), U16.15 (SDA), U17.4 (SDA)
SWIO: J2.1, J3.16, U4.18 (PD1)
TX0: J3.6, R3.2, R35.1, U4.2 (PD5)
TX1: J3.4, R37.2, TX1.1, U2.16 (TXD)
V-S: C6.1, C7.1, J4.4, J4.5, J4.6, J4.18, J5.4, R23.1, U1.5 (VS), U12.5 (LED_A), U12.8 (VCC), U13.5 (VDD), U15.3 (VBAT), U15.8 (VCC), U16.2 (VCC), U16.14 (VBAT), U17.1 (VCC)
WAKE: J3.7, U2.5 (GPIO14), U4.8 (PD0)
iin: J4.13, P1.1, R14.2, U1.8 (IN+)
iout: C2.1, J1.A4 (VBUS), J1.A9 (VBUS), J1.B4 (VBUS), J1.B9 (VBUS), J4.14, R12.2, R14.1, U1.7 (IN-), U7.3 (VI)
